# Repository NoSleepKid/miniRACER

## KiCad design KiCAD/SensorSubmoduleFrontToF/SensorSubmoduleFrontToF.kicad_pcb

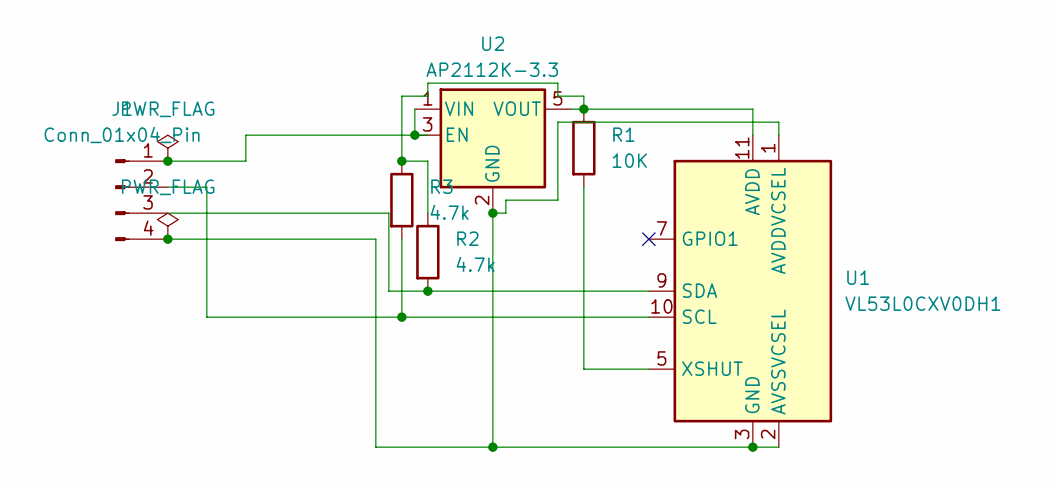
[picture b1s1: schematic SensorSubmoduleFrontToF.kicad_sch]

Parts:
J1: Conn_01x04_Pin; PinHeader_1x04_P1.00mm_Vertical
R1: 10K; R_0603_1608Metric
R2, R3: 4.7k; R_0603_1608Metric
U1: VL53L0CXV0DH1; ST_VL53L1x
U2: AP2112K-3.3; SOT-23-5

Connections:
unnamed: J1.1, U2.1 (VIN), U2.3 (EN)
unnamed: J1.2, R3.2, U1.10 (SCL)
unnamed: J1.3, R2.2, U1.9 (SDA)
unnamed: J1.4, U1.1 (AVDDVCSEL), U1.2 (AVSSVCSEL), U1.3 (GND), U1.4 (GND), U1.6 (GND), U1.12 (GND), U2.2 (GND)
unnamed: R1.1, R2.1, R3.1, U1.11 (AVDD), U2.5 (VOUT)
unnamed: R1.2, U1.5 (XSHUT)

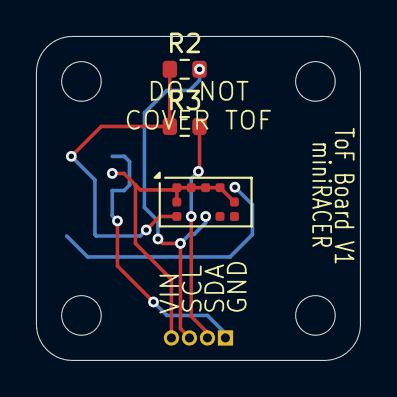
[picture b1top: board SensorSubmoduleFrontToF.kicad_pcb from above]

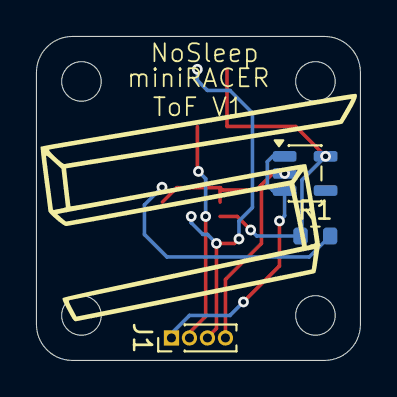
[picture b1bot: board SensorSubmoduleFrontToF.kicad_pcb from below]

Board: 2 copper layers, 18.0 x 18.0 mm, 6 parts (3 on the bottom side), 6 nets.

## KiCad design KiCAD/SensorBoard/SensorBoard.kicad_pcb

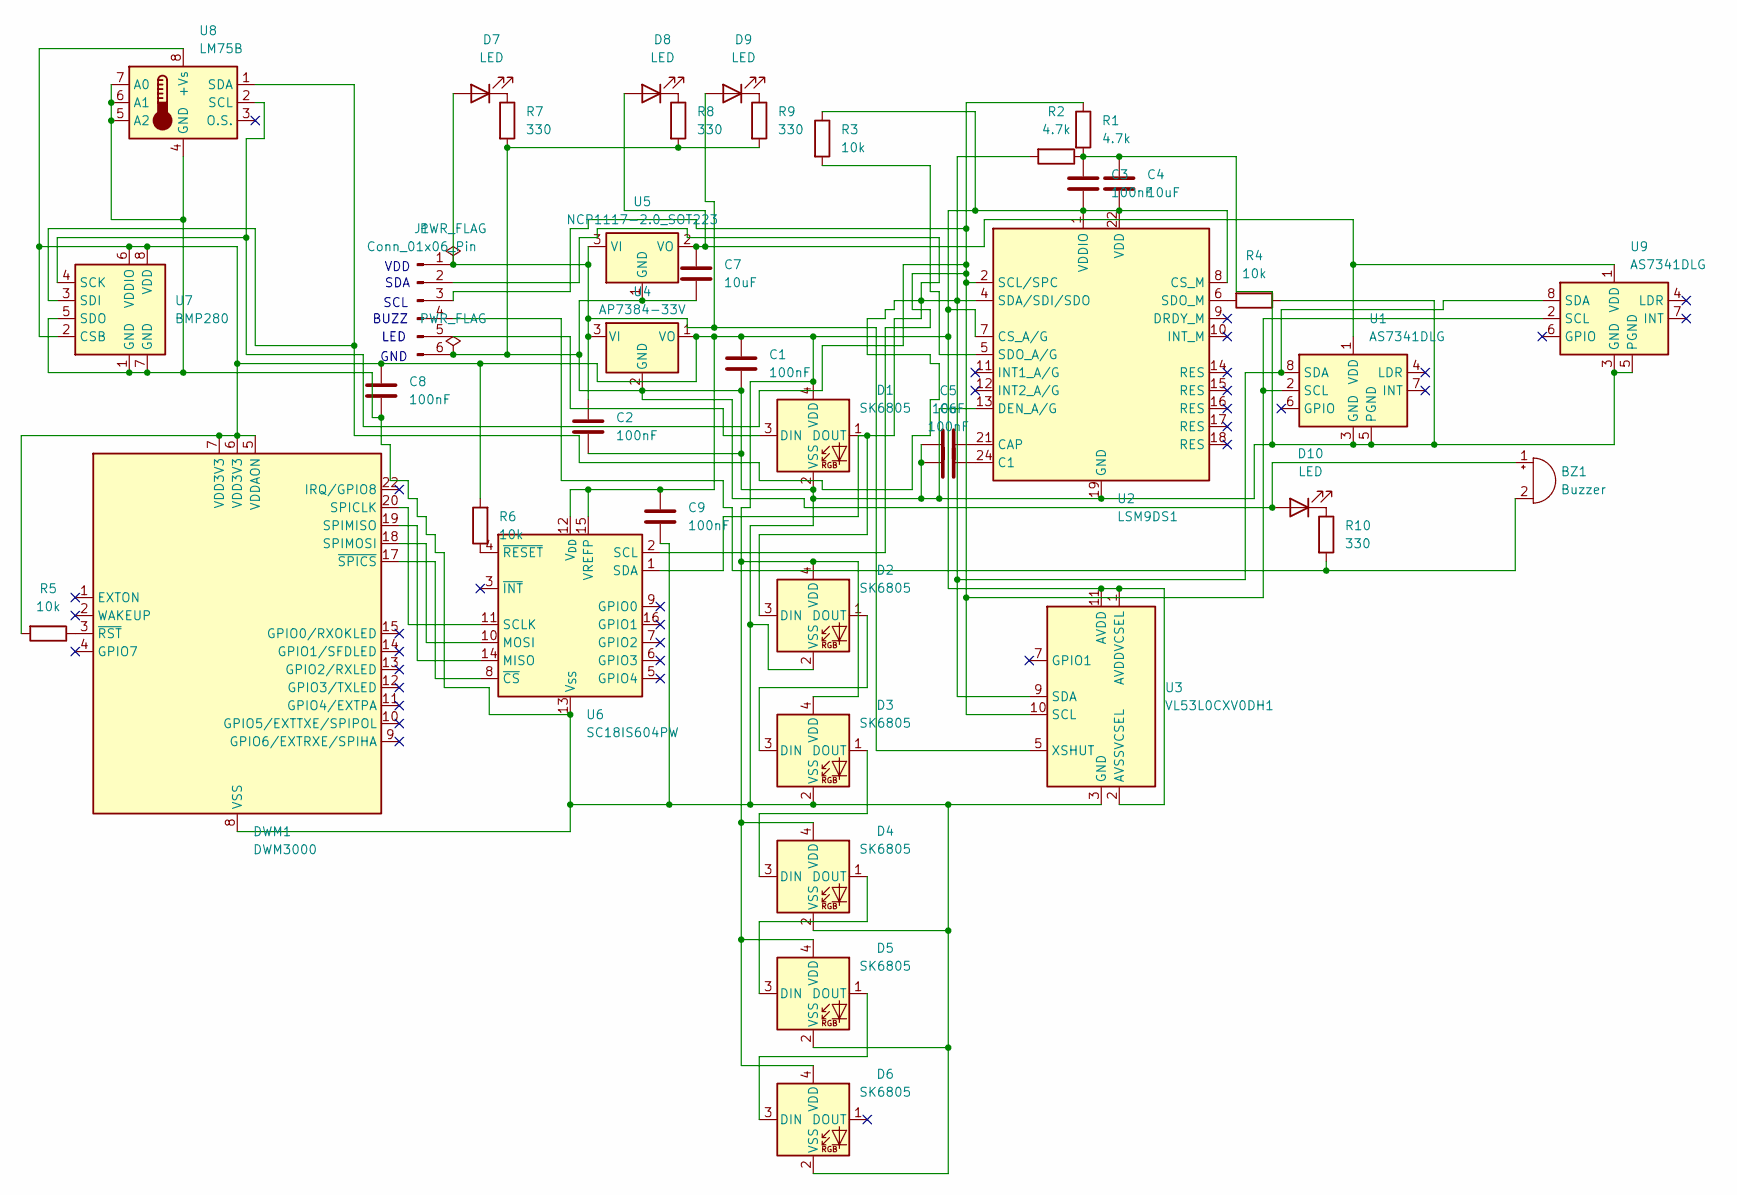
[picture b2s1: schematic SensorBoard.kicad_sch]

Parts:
BZ1: Buzzer; Buzzer_12x9.5RM7.6
C1, C2, C3, C6, C8, C9: 100nF; C_0805_2012Metric
C4, C5, C7: 10uF; C_0805_2012Metric
D1, D2, D3, D4, D5, D6: SK6805; LED_SK6805_PLCC4_2.4x2.7mm_P1.3mm
D7, D8, D9, D10: LED; LED_0805_2012Metric
DWM1: DWM3000; DWM1000
J1: Conn_01x06_Pin; PinHeader_1x06_P1.00mm_Vertical
R1, R2: 4.7k; R_0603_1608Metric
R3, R4, R5, R6: 10k; R_0603_1608Metric
R7, R8, R9, R10: 330; R_0805_2012Metric
U1, U9: AS7341DLG; AMS_OLGA-8_2x3.1mm_P0.8mm
U2: LSM9DS1; LGA-24L_3x3.5mm_P0.43mm
U3: VL53L0CXV0DH1; ST_VL53L1x
U4: AP7384-33V; TO-92_Inline_Wide
U5: NCP1117-2.0_SOT223; SOT-223-3_TabPin2
U6: SC18IS604PW; TSSOP-16_4.4x5mm_P0.65mm
U7: BMP280; Bosch_LGA-8_2x2.5mm_P0.65mm_ClockwisePinNumbering
U8: LM75B; SOIC-8_3.9x4.9mm_P1.27mm

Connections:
unnamed: BZ1.1 (+), C1.2, C2.2, C3.1, C4.1, C5.2, C6.2, C7.2, C8.2, C9.2, D1.2 (VSS), D2.2 (VSS), D3.2 (VSS), D4.2 (VSS), D5.2 (VSS), D6.2 (VSS), D10.2 (A), DWM1.8 (VSS), DWM1.16 (VSS), DWM1.21 (VSS), DWM1.23 (VSS), DWM1.24 (VSS), J1.6, R1.2, R2.1, R4.1, R7.2, R8.2, R9.2, U1.3 (GND), U1.5 (PGND), U2.13 (DEN_A/G), U2.19 (GND), U2.20 (GND), U3.3 (GND), U3.4 (GND), U3.6 (GND), U3.12 (GND), U4.2 (GND), U5.1 (GND), U6.13 (V_{SS}), U7.1 (GND), U7.5 (SDO), U7.7 (GND), U8.4 (GND), U8.5 (A2), U8.6 (A1), U8.7 (A0), U9.3 (GND), U9.5 (PGND)
unnamed: BZ1.2 (-), J1.4, R10.2
unnamed: D1.3 (DIN), J1.5
unnamed: D1.1 (DOUT), D2.3 (DIN), J1.2, R2.2, U1.8 (SDA), U2.4 (SDA/SDI/SDO), U3.9 (SDA), U6.1 (SDA), U7.3 (SDI), U8.1 (SDA), U9.8 (SDA)
unnamed: C1.1, C3.2, C4.2, C8.1, C9.1, D1.4 (VDD), D2.4 (VDD), D3.4 (VDD), D4.4 (VDD), D5.4 (VDD), D6.4 (VDD), DWM1.5 (VDDAON), DWM1.6 (VDD3V3), DWM1.7 (VDD3V3), R3.1, R5.2, R6.2, U2.1 (VDDIO), U2.3 (VDDIO), U2.7 (CS_A/G), U2.8 (CS_M), U2.22 (VDD), U2.23 (VDD), U3.1 (AVDDVCSEL), U3.2 (AVSSVCSEL), U3.11 (AVDD), U4.1 (VO), U6.12 (V_{DD}), U6.15 (VREFP), U7.2 (CSB), U7.6 (VDDIO), U7.8 (VDD), U8.8 (+Vs)
unnamed: D2.1 (DOUT), D3.3 (DIN)
unnamed: D3.1 (DOUT), D4.3 (DIN)
unnamed: D4.1 (DOUT), D5.3 (DIN)
unnamed: D5.1 (DOUT), D6.3 (DIN)
unnamed: C2.1, D7.2 (A), D9.2 (A), J1.1, U3.5 (XSHUT), U4.3 (VI), U5.3 (VI)
unnamed: D7.1 (K), R7.1
unnamed: C7.1, D8.2 (A), U1.1 (VDD), U5.2 (VO), U9.1 (VDD)
unnamed: D8.1 (K), R8.1
unnamed: D9.1 (K), R9.1
unnamed: D10.1 (K), R10.1
unnamed: DWM1.20 (SPICLK), U6.11 (SCLK)
unnamed: DWM1.19 (SPIMISO), U6.14 (MISO)
unnamed: DWM1.18 (SPIMOSI), U6.10 (MOSI)
unnamed: DWM1.3 (~RST), R5.1
unnamed: DWM1.17 (~SPICS), U6.8 (~CS)
unnamed: J1.3, R1.1, U1.2 (SCL), U2.2 (SCL/SPC), U3.10 (SCL), U6.2 (SCL), U7.4 (SCK), U8.2 (SCL), U9.2 (SCL)
unnamed: C6.1, U2.24 (C1)
unnamed: C5.1, U2.21 (CAP)
unnamed: R3.2, U2.5 (SDO_A/G)
unnamed: R4.2, U2.6 (SDO_M)
unnamed: R6.1, U6.4 (~RESET)

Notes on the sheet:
SCL
LED
SDA
VDD
GND
BUZZ

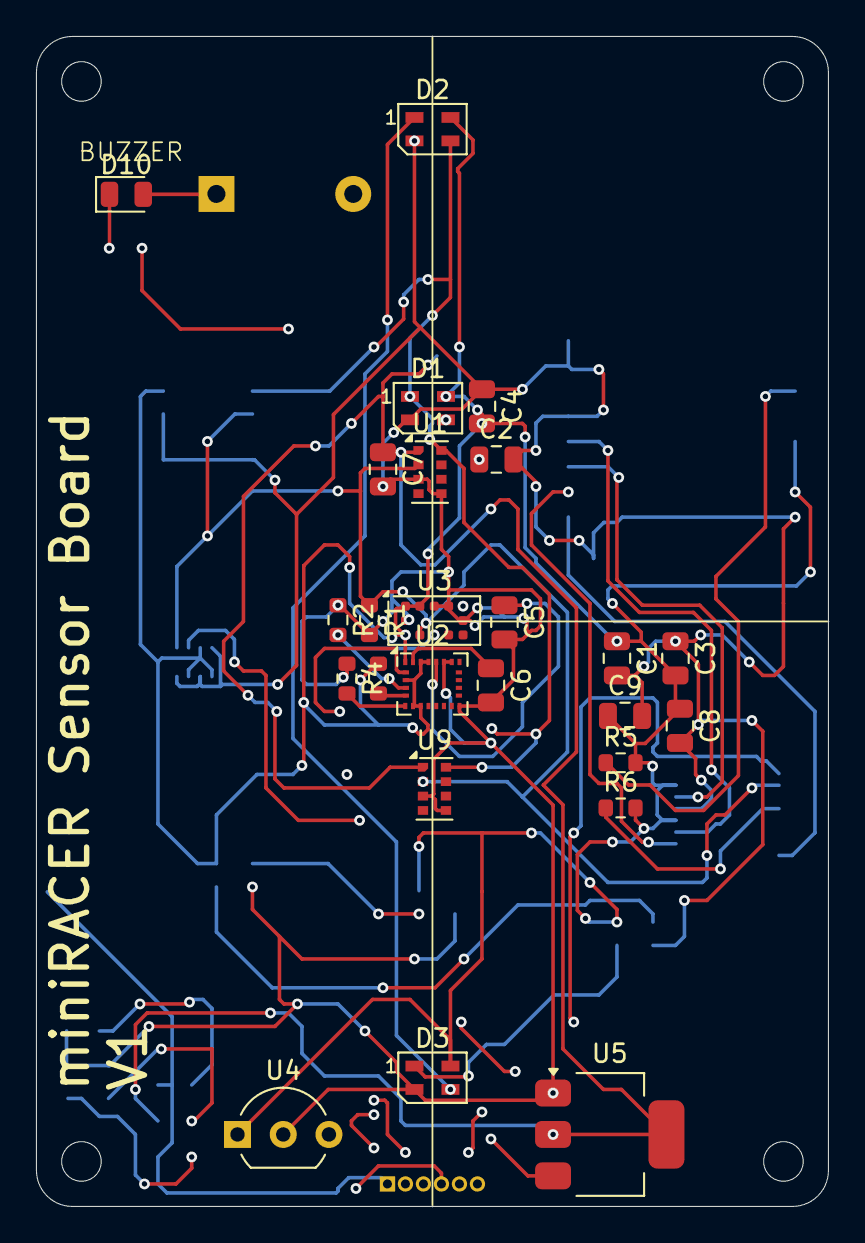
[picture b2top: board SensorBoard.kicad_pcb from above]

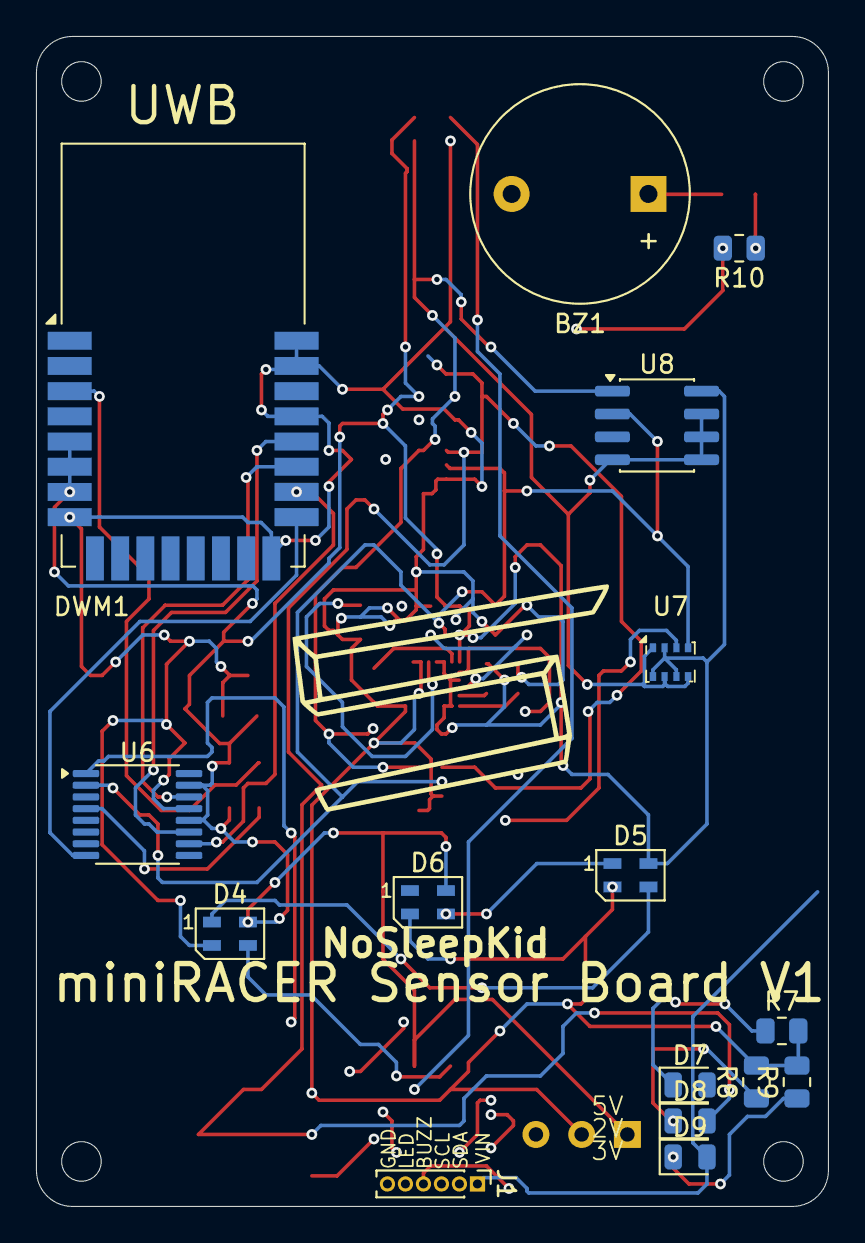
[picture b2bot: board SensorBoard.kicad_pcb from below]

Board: 4 copper layers, 44.0 x 65.0 mm, 41 parts (16 on the bottom side), 26 nets.

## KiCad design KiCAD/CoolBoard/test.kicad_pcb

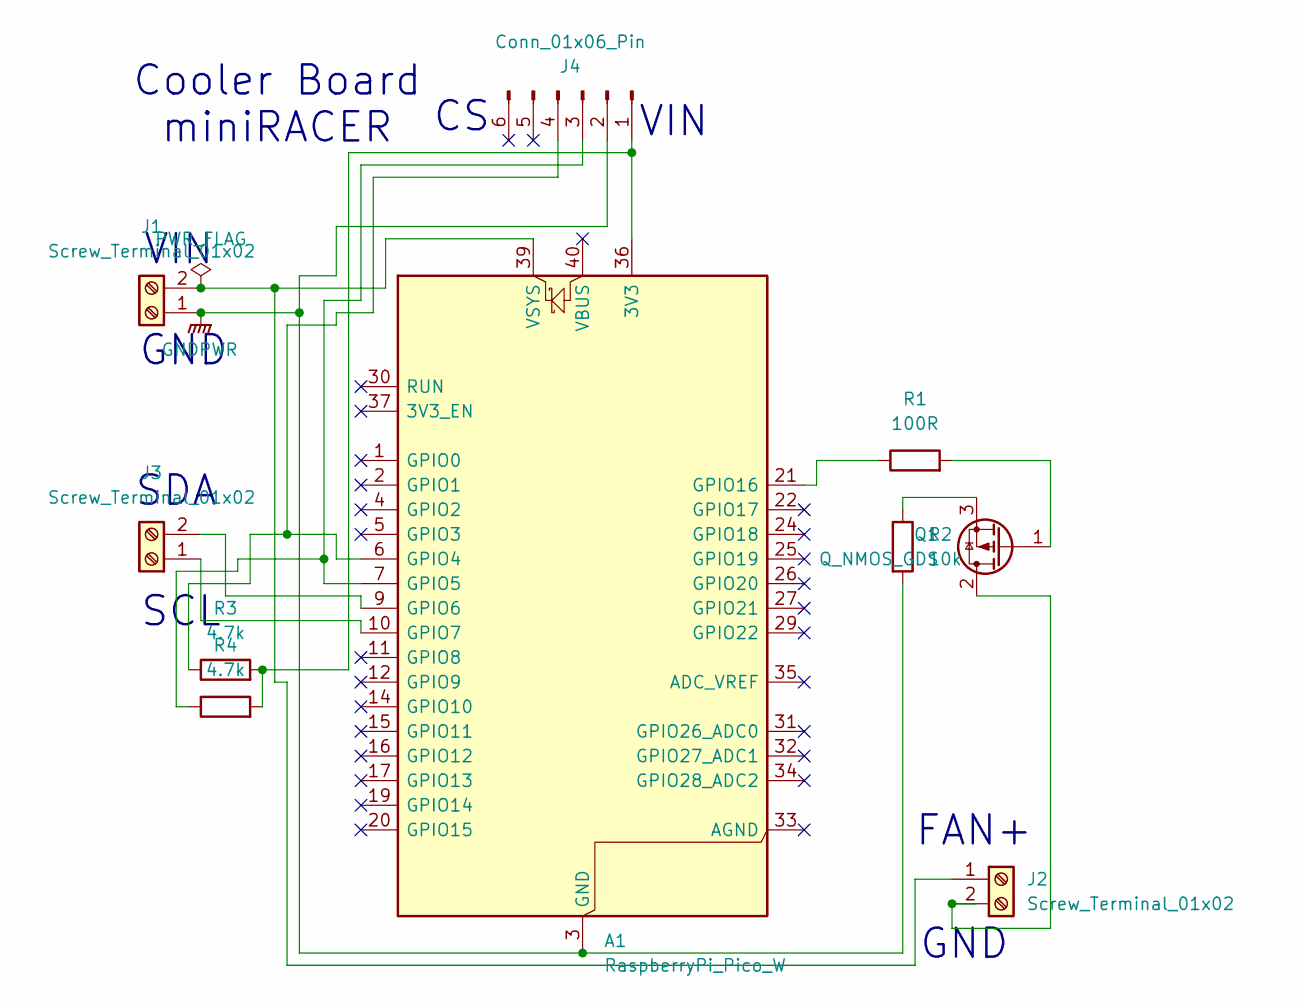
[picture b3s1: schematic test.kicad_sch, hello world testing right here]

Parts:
A1: RaspberryPi_Pico_W; RaspberryPi_Pico_Common_THT
J1, J2, J3: Screw_Terminal_01x02; TerminalBlock_Phoenix_MKDS-1,5-2-5.08_1x02_P5.08mm_Horizont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
J4: Conn_01x06_Pin; PinHeader_1x06_P2.54mm_Vertical
Q1: Q_NMOS_GDS; TO-220-3_Vertical
R1: 100R; R_0805_2012Metric
R2: 10k; R_0805_2012Metric
R3, R4: 4.7k; R_0805_2012Metric

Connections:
GNDPWR: A1.3 (GND), A1.8 (GND), A1.13 (GND), A1.18 (GND), A1.23 (GND), A1.28 (GND), A1.38 (GND), J1.1, J4.2, R2.2
unnamed: A1.36 (3V3), J4.1, R3.2, R4.2
unnamed: A1.6 (GPIO4), J4.4, R3.1
unnamed: A1.7 (GPIO5), J4.3, R4.1
unnamed: A1.9 (GPIO6), J3.2
unnamed: A1.10 (GPIO7), J3.1
unnamed: A1.21 (GPIO16), R1.1
unnamed: A1.39 (VSYS), J1.2, J2.1
unnamed: J2.2, Q1.2 (D)
unnamed: Q1.1 (G), R1.2
unnamed: Q1.3 (S), R2.1

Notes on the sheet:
VIN
SCL
Cooler Board miniRACER
FAN+
SDA
GND
GND

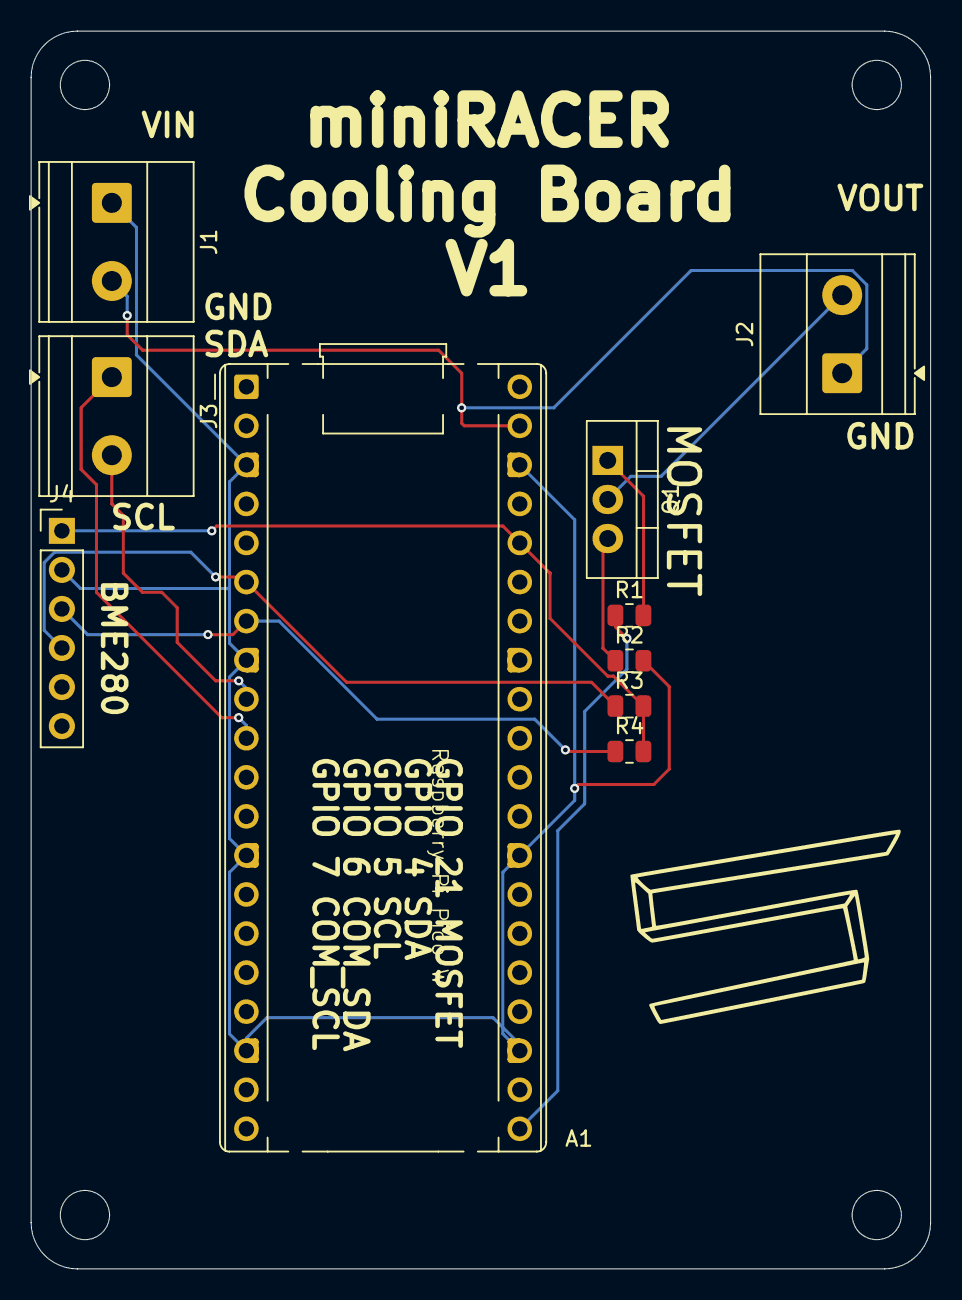
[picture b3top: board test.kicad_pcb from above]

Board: 2 copper layers, 58.5 x 80.5 mm, 10 parts (0 on the bottom side), 11 nets.

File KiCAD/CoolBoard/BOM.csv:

Id;Designator;Mfg Part #;Description;Qty;Designation;Footprint;Type
1;J1, J2, J3;TB002-500-02BE;TERMINAL BLOCK, SCREW TYPE, 5.00;3;Screw_Terminal_01x02;TerminalBlock_Phoenix_MKDS-1,5-2-5.08_1x02_P5.08mm_Horizontal;THT
2;J4;SSK01-MPH-254-A6;2.54MM MALE HEADER 1X6PIN, STRAI;1;Conn_01x06_Pin;PinHeader_1x06_P2.54mm_Vertical;THT
4;R1;RP0805CT-1000GN-96TR;8W 100OHM BEO RF CHIP RESISTOR W;1;100R;R_0805_2012Metric;SMD
5;R2;RMCF0402FT10K0;RES 10K OHM 1% 1/16W 0402;1;10k;R_0805_2012Metric;SMD
6;R3, R4;RC0402JR-074K7L;RES 4.7K OHM 5% 1/16W 0402;2;4.7k;R_0805_2012Metric;SND
